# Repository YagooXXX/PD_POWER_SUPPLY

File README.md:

PD诱骗9V电压
MT3608  BOOST  +12V
TPS5430  BUCK  -12V

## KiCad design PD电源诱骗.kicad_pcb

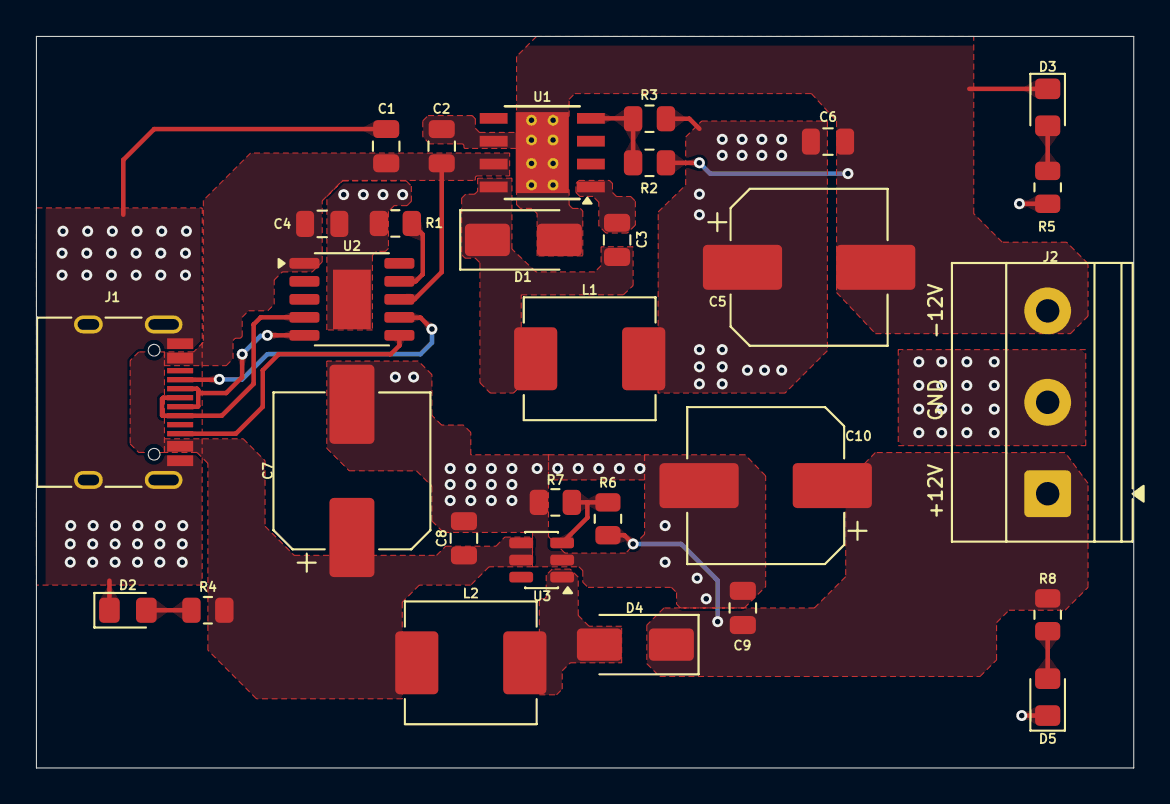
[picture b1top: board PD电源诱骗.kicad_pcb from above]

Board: 2 copper layers, 61.0 x 40.6 mm, 30 parts (0 on the bottom side), 17 nets.

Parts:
C1, C2: 10uF; C_0805_2012Metric
C3, C6: 100nF; C_0805_2012Metric
C4, C8, C9: 1uF; C_0805_2012Metric
C5, C7, C10: 220uF/25V; CP_Elec_8x10.5
D1, D4: SS36; D_SMA
D2: LED RED; LED_0805_2012Metric_Pad1.15x1.40mm_HandSolder
D3: LED BLUE; LED_0805_2012Metric_Pad1.15x1.40mm_HandSolder
D5: LED GREEN; LED_0805_2012Metric_Pad1.15x1.40mm_HandSolder
J1: USB_C_Receptacle_USB2.0_16P; USB_C_Receptacle_HRO_TYPE-C-31-M-12
J2: 电源IO; TerminalBlock_Phoenix_MKDS-1,5-3-5.08_1x03_P5.08mm_Horizont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
L1, L2: 22uH; L_TechFuse_SL0630
R1: 6.8K; R_0805_2012Metric
R2: 89K; R_0805_2012Metric
R3: 10K; R_0805_2012Metric
R4: 4K; R_0805_2012Metric
R5, R8: 5K; R_0805_2012Metric
R6: 39K; R_0805_2012Metric
R7: 2K; R_0805_2012Metric
U1: TPS5430DDA; TI_SO-PowerPAD-8_ThermalVias
U2: CH224A; SSOP-10-1EP_3.9x4.9mm_P1mm_EP2.1x3.3mm
U3: MT3608; SOT-23-6

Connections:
+12V: C9.1, C10.1, D4.1 (K), J2.1, R6.1, R8.1
-12V: C2.2, C5.2, C6.1, D1.2 (A), D3.1 (K), J2.3, R3.2, U1.6 (GND), U1.9 (GNDPAD)
/R_REF: R1.1, U2.9 (CFG1)
GND: C1.2, C4.1, C5.1, C6.2, C7.2, C8.2, C9.2, C10.2, D2.1 (K), D5.1 (K), J1.A1 (GND), J1.A12 (GND), J1.S1 (SHIELD), J2.2, L1.2, R1.2, R2.1, R5.1, R7.2, U2.11 (GND), U3.2 (GND)
unnamed: C3.2, D1.1 (K), L1.1, U1.8 (PH)
unnamed: D2.2 (A), R4.2
unnamed: D3.2 (A), R5.2
unnamed: D4.2 (A), L2.2, U3.1 (SW)
unnamed: D5.2 (A), R8.2
unnamed: J1.A5 (CC1), U2.7 (CC1)
unnamed: J1.B5 (CC2), U2.6 (CC2)
unnamed: C3.1, U1.1 (BOOT)
unnamed: R2.2, R3.1, U1.4 (VSENSE)
unnamed: J1.A7 (D-), J1.B7 (D-), U2.5 (DM)
unnamed: J1.A6 (D+), J1.B6 (D+), U2.4 (DP)
unnamed: R6.2, R7.1, U3.3 (FB)
VCC: C1.1, C2.1, C4.2, C7.1, C8.1, J1.A4 (VBUS), J1.A9 (VBUS), L2.1, R4.1, U1.7 (VIN), U2.1 (VHV), U2.8 (VBUS), U3.4 (EN), U3.5 (IN)

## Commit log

2026-01-15 V1.0 Initial Release
2026-01-16 修改为诱骗9V+BOOST得到12V
2026-01-16 V2，更改诱骗电压为+9V
2026-01-16 update BOM
2026-01-16 Add power supply specifications to README
2026-03-10 Correct MT3602 to MT3608 in README
